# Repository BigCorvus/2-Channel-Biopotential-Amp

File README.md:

# 2-Channel-Biopotential-Amp
A small general purpose biopotential amplifier for ECG/EEG/EMG measurements based on the TI INA2321 dual instrumentation amplifier. The device can be connected to any ADC or microcontroller with built-in ADC.

These can be stacked together to easily increase the channel count of your system.

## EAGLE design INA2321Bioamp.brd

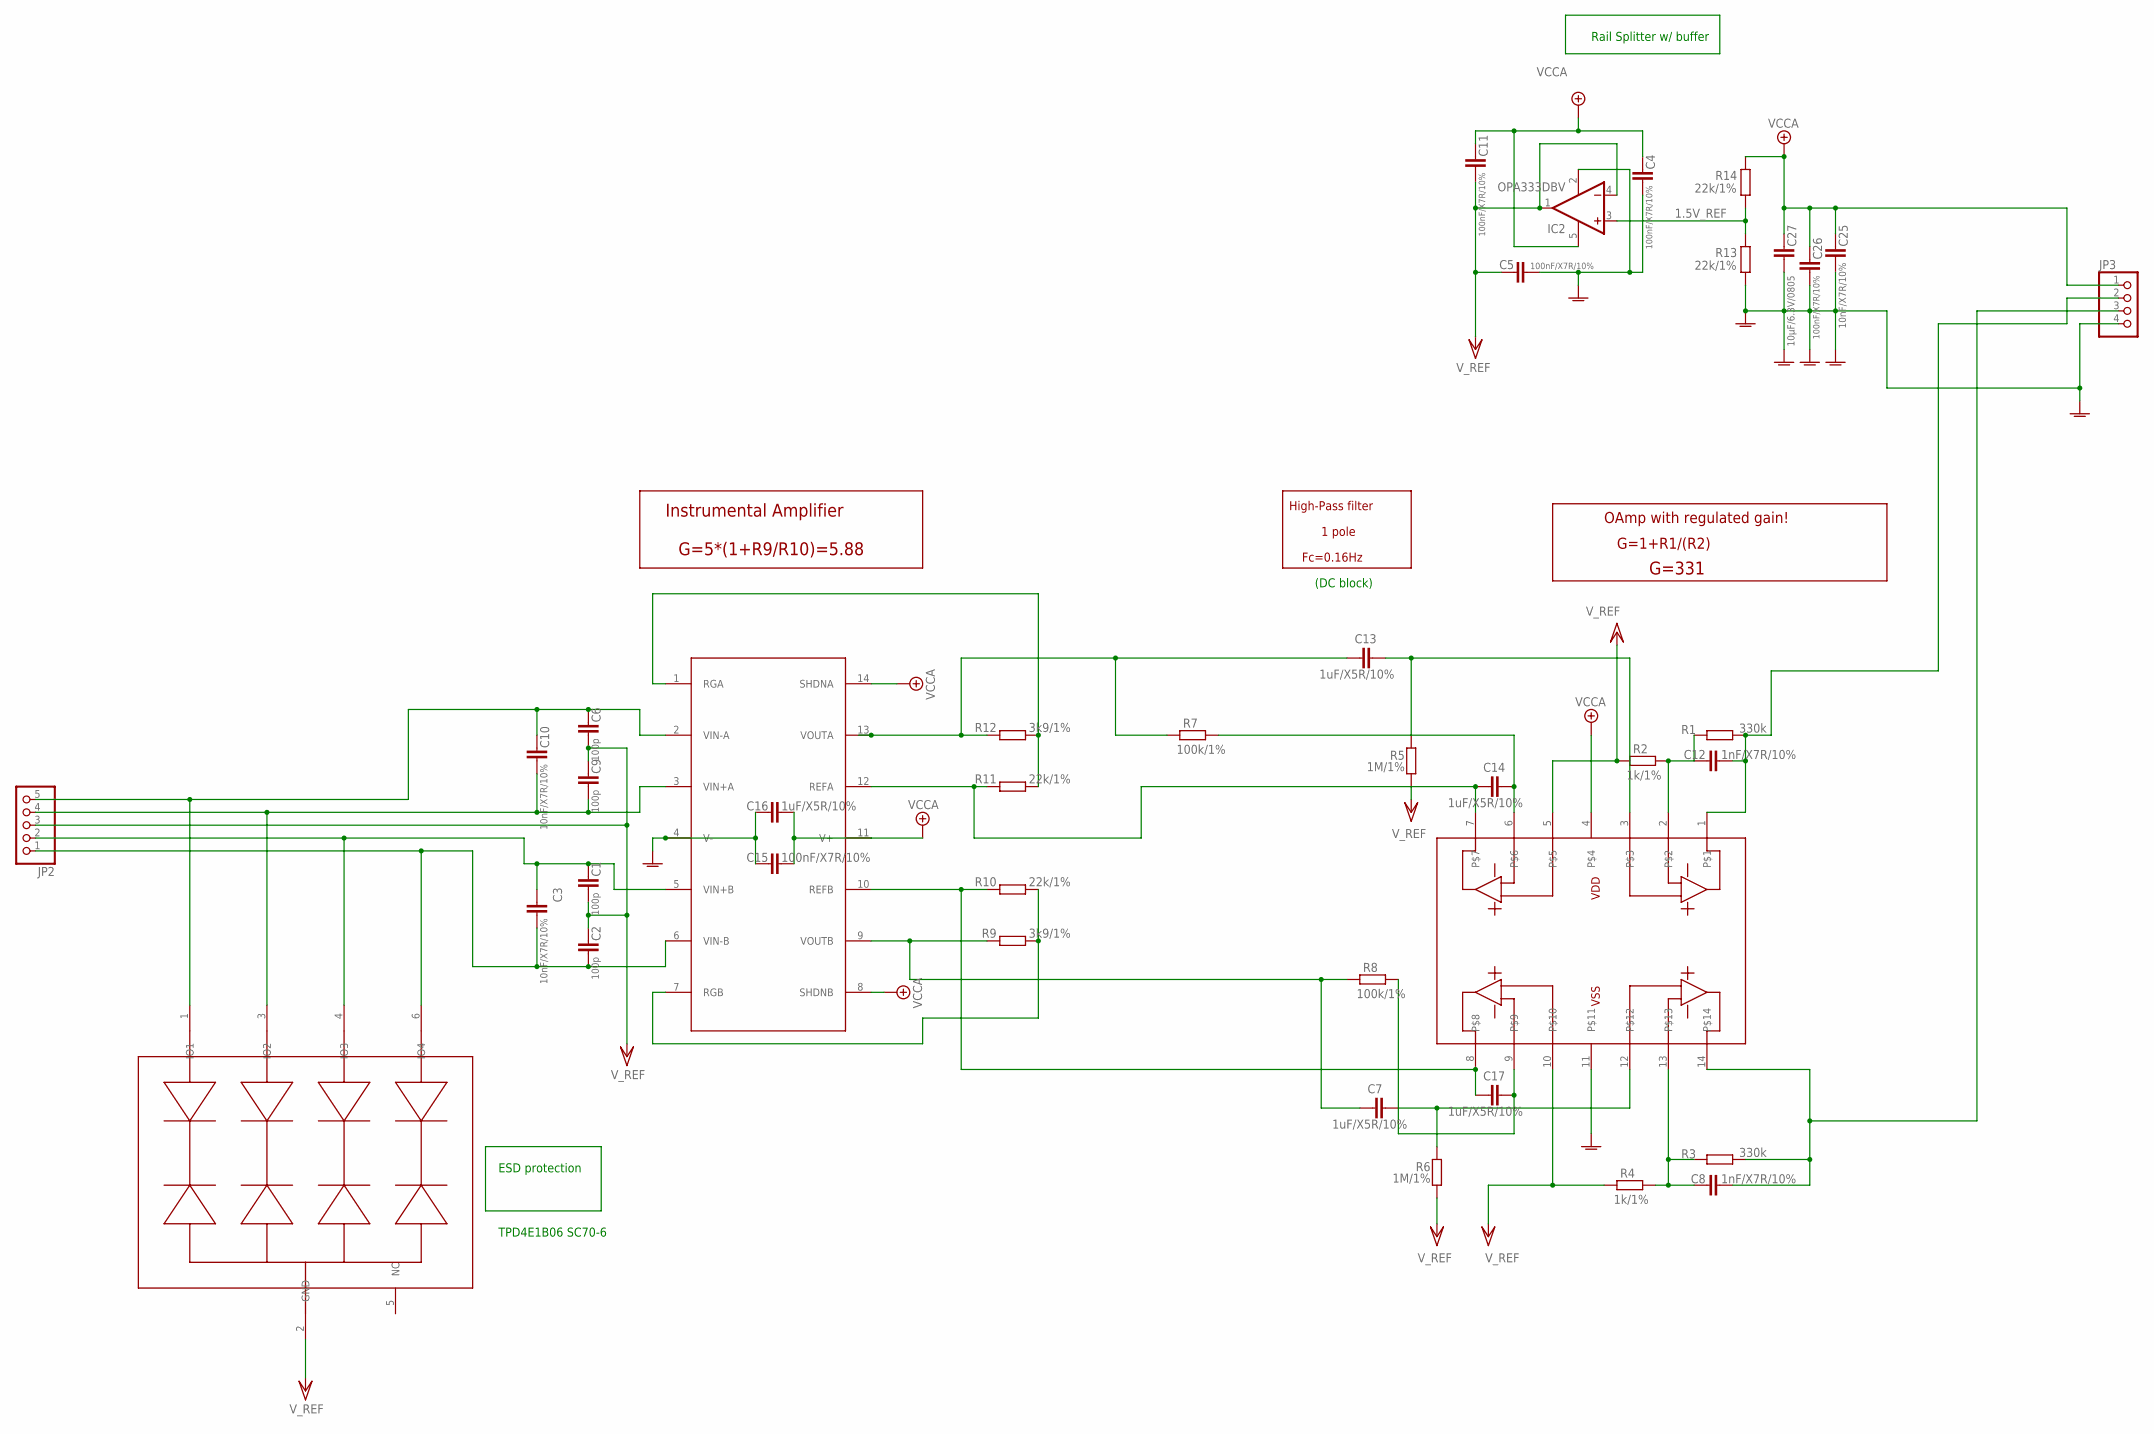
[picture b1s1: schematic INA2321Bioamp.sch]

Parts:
C1, C2, C6, C9: 100p; C0603_DWS
C3, C10, C25: 10nF/X7R/10%; C0603_DWS
C4, C5, C11, C15, C26: 100nF/X7R/10%; C0603_DWS
C7, C13, C14, C16, C17: 1uF/X5R/10%; C0603_DWS
C8, C12: 1nF/X7R/10%; C0603_DWS
C27: 10µF/6.3V/0805; C0805_5MIL_DWS
IC2: OPA333DBV; SOT23-5
JP2: PINHD-1X5; 1X05
JP3: PINHD-1X4; 1X04
R1, R3: 330k; R0603_5MIL_DWS
R2, R4: 1k/1%; R0603_5MIL_DWS
R5, R6: 1M/1%; R0603_5MIL_DWS
R7, R8: 100k/1%; R0603_5MIL_DWS
R9, R12: 3k9/1%; R0603_5MIL_DWS
R10, R11, R13, R14: 22k/1%; R0603_5MIL_DWS
U$1: INA2321; TSSOP14
U$2: TPD4E1B06; SC70-6L
U$3: MCP609; TSSOP14

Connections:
1.5V_REF: IC2.3 (+IN), R13.2, R14.1
+5V: C4.1, C11.1, C15.2, C16.2, C25.1, C26.1, C27.1, IC2.5 (V+), JP3.1, R14.2, U$1.8 (SHDNB), U$1.11 (V+), U$1.14 (SHDNA), U$3.4
GNDA: C4.2, C5.2, C15.1, C16.1, C25.2, C26.2, C27.2, IC2.2 (V-), JP3.4, R13.1, U$1.4 (V-), U$3.11
unnamed: C8.2, JP3.3, R3.2, U$3.14
unnamed: C6.1, C10.1, JP2.5, U$1.2 (VIN-A), U$2.1 (IO1)
unnamed: C13.1, R7.2, R12.2, U$1.13 (VOUTA)
unnamed: R11.1, R12.1, U$1.1 (RGA)
unnamed: C13.2, R5.1, U$3.3
unnamed: C12.1, R1.1, R2.1, U$3.2
unnamed: C12.2, JP3.2, R1.2, U$3.1
unnamed: C9.2, C10.2, JP2.4, U$1.3 (VIN+A), U$2.3 (IO2)
unnamed: R9.1, R10.1, U$1.7 (RGB)
unnamed: C1.1, C3.1, JP2.2, U$1.5 (VIN+B), U$2.4 (IO3)
unnamed: C2.2, C3.2, JP2.1, U$1.6 (VIN-B), U$2.6 (IO4)
unnamed: C14.2, R7.1, U$3.6
unnamed: C17.2, R8.1, U$3.9
unnamed: C17.1, R10.2, U$1.10 (REFB), U$3.8
unnamed: C14.1, R11.2, U$1.12 (REFA), U$3.7
unnamed: C7.2, R6.1, U$3.12
unnamed: C7.1, R8.2, R9.2, U$1.9 (VOUTB)
unnamed: C8.1, R3.1, R4.1, U$3.13
VCC/2: C1.2, C2.1, C5.1, C6.2, C9.1, C11.2, IC2.1 (OUT), IC2.4 (-IN), JP2.3, R2.2, R4.2, R5.2, R6.2, U$2.2 (GND), U$3.5, U$3.10

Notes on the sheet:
G=1+R1/(R2)
G=331
Fc=0.16Hz
High-Pass filter
OAmp with regulated gain!
1 pole
G=5*(1+R9/R10)=5.88
Instrumental Amplifier
(DC block)
Rail Splitter w/ buffer
TPD4E1B06 SC70-6
ESD protection

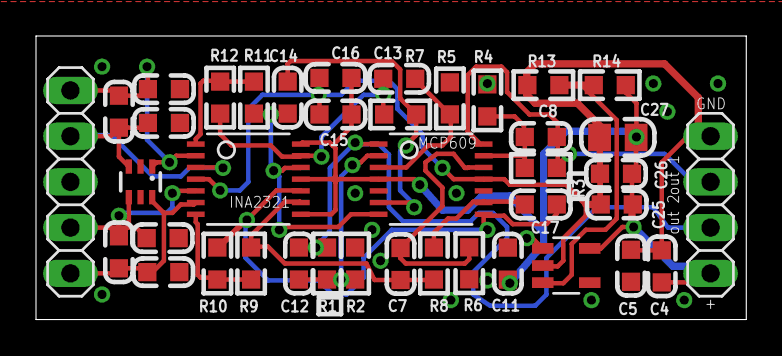
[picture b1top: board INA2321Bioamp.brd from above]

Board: 2 copper layers, 39.5 x 15.8 mm, 40 parts (0 on the bottom side), 22 nets.

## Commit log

2020-03-20 Create LICENSE
